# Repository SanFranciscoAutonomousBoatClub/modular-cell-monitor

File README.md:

# modular-cell-monitor

6820-differential-interface: A differential SPI interface for the LTC6820 compatable with the LTC6811.

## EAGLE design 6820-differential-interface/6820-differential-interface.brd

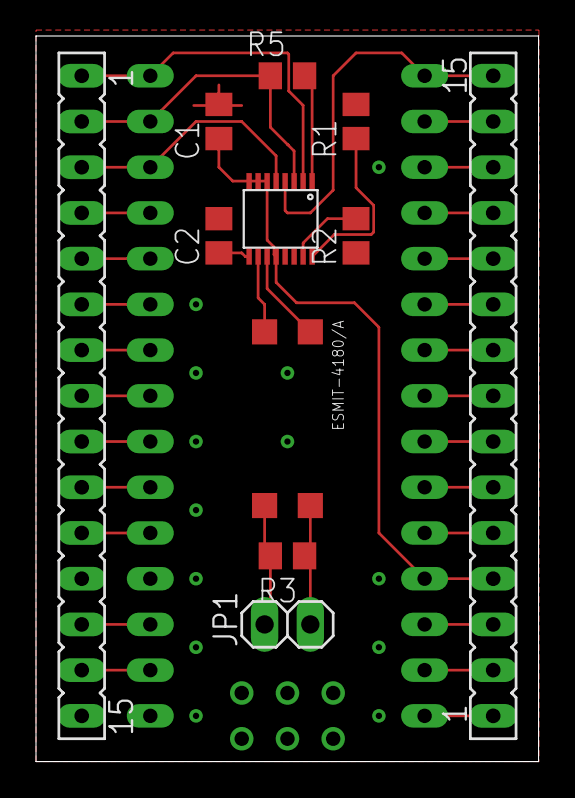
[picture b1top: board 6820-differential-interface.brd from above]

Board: 2 copper layers, 27.9 x 40.3 mm, 12 parts (1 on the bottom side), 36 nets.

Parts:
C1, C2: 100nF; C0805
JP1: 1X02
R1: 1.21k; R0805
R2: 806; R0805
R3: R0805
R5: 5k; R0805
SV1, SV2: FE15
U$1: NANO
U$2: LTC6820; MSOP-16
U$3: ESMIT-4180/A

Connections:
+5V: C1.2, R5.1, SV1.4, U$1.5V, U$2.1, U$2.6, U$2.7, U$2.8, U$2.12
GND: C2.2, R2.1, U$2.13, U$2.14
unnamed: R1.1, U$2.16
unnamed: R1.2, R2.2, U$2.15
unnamed: SV2.1, U$1.D12, U$2.2
unnamed: C2.1, U$2.9
unnamed: SV1.15, U$1.D13, U$2.4
unnamed: R5.2, SV2.2, U$1.D11, U$2.3
unnamed: SV1.14, U$1.3.3V
unnamed: SV1.13, U$1.AREF
unnamed: SV1.12, U$1.A0
unnamed: SV1.11, U$1.A1
unnamed: SV1.10, U$1.A2
unnamed: SV1.9, U$1.A3
unnamed: SV2.3, U$1.D10, U$2.5
unnamed: SV2.4, U$1.D9
unnamed: SV2.5, U$1.D8
unnamed: SV2.6, U$1.D7
unnamed: SV2.7, U$1.D6
unnamed: SV2.8, U$1.D5
unnamed: SV2.9, U$1.D4
unnamed: SV2.10, U$1.D3
unnamed: SV2.11, U$1.D2
unnamed: SV2.13, U$1.RST1
unnamed: SV2.14, U$1.RX1
unnamed: SV1.1, U$1.RAW
unnamed: SV1.2, U$1.GND
unnamed: SV1.3, U$1.RST
unnamed: SV1.5, U$1.A7
unnamed: SV1.6, U$1.A6
unnamed: SV1.7, U$1.A5
unnamed: SV1.8, U$1.A4
unnamed: U$2.11, U$3.1
unnamed: U$2.10, U$3.2
unnamed: JP1.1, R3.2, U$3.3
unnamed: JP1.2, R3.1, U$3.4

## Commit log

2017-07-27 Added LTC6820 Differential Interface board
2017-07-27 moved 6820-differential-interface to its directory, updated readme
2017-07-27 added images of the 6820 board
2017-07-27 updated images
2017-07-27 changed image size
2017-07-27 changed width
